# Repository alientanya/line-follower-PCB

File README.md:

# FLF Bot Modular PCB

A modular PCB platform for Fast Line Follower (FLF) robots, designed to prioritize sensor experimentation and component flexibility.
This board allows multiple sensor array designs to be used interchangeably without redesigning the core electronics.
Instead of committing to a single sensor layout, this PCB supports four distinct sensor array designs, all compatible with the same base system.

---

## Menu

- [Hardware Revisions](#hardware-revisions)
- [Repository Structure](#repository-structure)
- [Core Features](#core-features)  
- [Core Components & Design Choices](#core-components--design-choices)  
- [Sensors](#sensors)  
- [Interchangeable Sensor Arrays](#interchangeable-sensor-arrays)  
- [8+1 Sensor Placement Strategy](#81-sensor-placement-strategy)  
- [Main Control PCB](#main-control-pcb)  
- [MCU Control](#mcu-control)  
- [Detailed Module Documentation](#detailed-module-documentation)
- [Design Considerations](#design-considerations)  
- [License](#license)

---

## Hardware Revisions

- **Lavender 1.0 (Blackpill version)** —   
  Fully designed, fabricated, assembled, and successfully deployed on the physical FLF robot. Uses the STM32F411 Blackpill module.
- **Lavender 2.0 (IC version)** —   
  Work-in-progress experimental design integrating a discrete STM32F411 IC directly onto the PCB.

---

## Repository Structure

```text
├── Lavender 1.0 (Blackpill vers)/    # Hardware-verified revision used on the physical robot
│   ├── line follower simple.kicad_pcb # Main body PCB layout
│   ├── line follower simple.kicad_sch # Main body schematic
│   ├── QRE1113.kicad_sch              # 16-Sensor QRE1113 schematic
│   ├── TCRT_sensors.kicad_sch         # 9-Sensor TCRT5000 schematic
│   ├── customssensor.kicad_sch        # Custom IR LED + PT334 schematic
│   ├── layerconnect.kicad_sch         # Inter-board connector schematic
│   └── FLF_gerbers/                   # Production Gerber output files
├── Lavender 2.0 (IC vers)/           # WIP prototype with discrete STM32 IC
│   ├── STMf411.kicad_sch              # Discrete STM32F411 MCU schematic
│   └── line follower simple.kicad_pcb # 2.0 PCB layout (WIP)
├── PCB customs/                       # 3D STEP models & custom KiCad footprint libraries
├── docs/                              # Detailed hardware documentation guides
│   ├── MODULES.md                     # Circuit modules & subsystem technical reference
│   ├── SENSOR_ARRAYS.md               # Sensor array designs & 8+1 strategy guide
│   └── PINOUTS_AND_REVISIONS.md       # Pin mapping & revision comparison guide
├── images/                            # PCB renders and schematic diagrams
├── LICENSE                            # MIT License
└── README.md                          # Main project README
```

---

## Core Features

* 4 interchangeable sensor array designs
* Modular architecture using headers
* STM32F411 (Blackpill) based control (Lavender 1.0)
* HC-05 Bluetooth connectivity
* Stackable PCB with internal battery space

---

## Core Components & Design Choices

### Microcontroller —  (Blackpill)

* High-speed ADC for sensor reading
* Rich GPIO availability
* Hardware timers for motor PWM
* Plug-in module → easy replacement

---

### Motor Driver — 

* Dual DC motor driver
* Efficient and compact
* Suitable for N20 motors

---

### Voltage Regulation — 

* Buck converter → stable 3.3V
* High efficiency for battery operation
* Adjustable output

---

### Communication — 

* UART-based Bluetooth module
* Used for debugging and tuning
* Supports STATE and EN pins

---

### Analog Multiplexer — 

* 16-channel analog MUX
* Used in high-density sensor configuration
* Reduces MCU pin usage

---

## Sensors

#### 

* Compact reflective IR sensor
* Fast response
* Used in high-density and simple arrays

#### 

* Larger footprint
* More tolerant of alignment and height

#### 

* Discrete design
* Custom Sensors
* Fully tunable sensitivity

---

## Interchangeable Sensor Arrays

All arrays share a common connector interface, making them plug-and-play.

### 1. 16-Sensor Curved Array (QRE1113 + MUX)

* High resolution                            
* Uses 74HC4067
* Designed for aggressive curves

### 2. 9-Sensor Straight Array (QRE1113)

* Direct MCU input
* Low latency
* Simpler processing

### 3. 9-Sensor Curved Array (TCRT5000)

* Better surface tolerance
* Slight curvature improves tracking

### 4. Custom Sensor Array

* IR LED + PT334-6C
* Fully customizable behaviour

---

## 8+1 Sensor Placement Strategy

* 8 main sensors → line tracking
* +1 front sensor → overshoot detection

Improves turning accuracy at high speed.

---

## MCU Control

The STM32F411 (Blackpill) acts as the central controller, interfacing with sensors, motor driver, and Bluetooth module.

* Reads sensor data:

  * Direct ADC (for 9-sensor arrays)
  * Via 74HC4067 MUX (for 16-sensor array)
* Processes line position
* Controls motors using PWM + direction pins (TB6612FNG)
* Handles UART communication with HC-05

All sensor arrays use a consistent interface, so firmware changes are minimal when switching configurations.

---

## Main Control PCB

This section describes the core board that handles control, power distribution, and user interaction.

* Hosts the STM32F411 (Blackpill), TB6612FNG motor driver, and HC-05 module
* Separates logic and motor power to reduce noise interference
* Includes dual switches:
  * Motor Kill
  * Battery Kill

* Provides connectors for all interchangeable sensor arrays
* Routes sensor signals (direct or via MUX) to the MCU
* Includes 2 push buttons:
  * Used for control, mode selection, and calibration
  * Hardware debounced (RC)
* Designed as part of a stacked PCB system:
  * Interfaces with the top board via pin headers
  * Creates space between layers for battery placement

---

## Detailed Module Documentation

Explore the dedicated hardware documentation guides for in-depth schematic breakdowns, pinout mappings, and circuit specifications:

- 🔌 **[Circuit Modules & Subsystems Guide](docs/MODULES.md)** — Technical reference for Power Management & Rail Isolation, MCU & SWD Debugging, TB6612FNG Motor Driver, 74HC4067 MUX, Emitter Biasing, RC Hardware Debouncing, and the Inter-Board Header Bus.
- 🎯 **[Interchangeable Sensor Arrays & Placement Strategy](docs/SENSOR_ARRAYS.md)** — Comprehensive breakdown of the 4 sensor array variants (16-QRE MUX, 9-QRE, 9-TCRT, Custom Discrete) and the 8+1 apex placement geometry.
- 📌 **[Pin Mapping & Hardware Revisions Guide](docs/PINOUTS_AND_REVISIONS.md)** — Hardware peripheral pin assignments (PWM, ADC, MUX select, UART), SWD interface, and comparison between Lavender 1.0 (Field-Tested) and Lavender 2.0 (WIP).

---

## Design Considerations

- Tradeoff between sensor resolution and sampling speed (MUX vs direct ADC)
- Separation of motor and logic power to reduce noise
- Modular sensor interface to allow rapid hardware iteration
- Use of off-the-shelf modules (MCU, driver, regulator) for reliability and easy replacement
- Support for multiple sensor geometries to evaluate performance under different track conditions

---

## Summary

Instead of locking the design into a single sensor configuration, this PCB is built as a flexible platform that encourages rapid experimentation and iteration. Supporting multiple interchangeable sensor arrays, it allows direct comparison between different sensing approaches, geometries, and component choices under the same hardware conditions. This makes it easier to fine-tune performance, optimise control algorithms, and adapt the system for different track types. Ultimately, the goal of this design is not just to work, but to provide a reliable foundation for continuously improving and pushing the limits of FLF performance.

---

## License

This project is licensed under the MIT License — see the [LICENSE](LICENSE) file for details.

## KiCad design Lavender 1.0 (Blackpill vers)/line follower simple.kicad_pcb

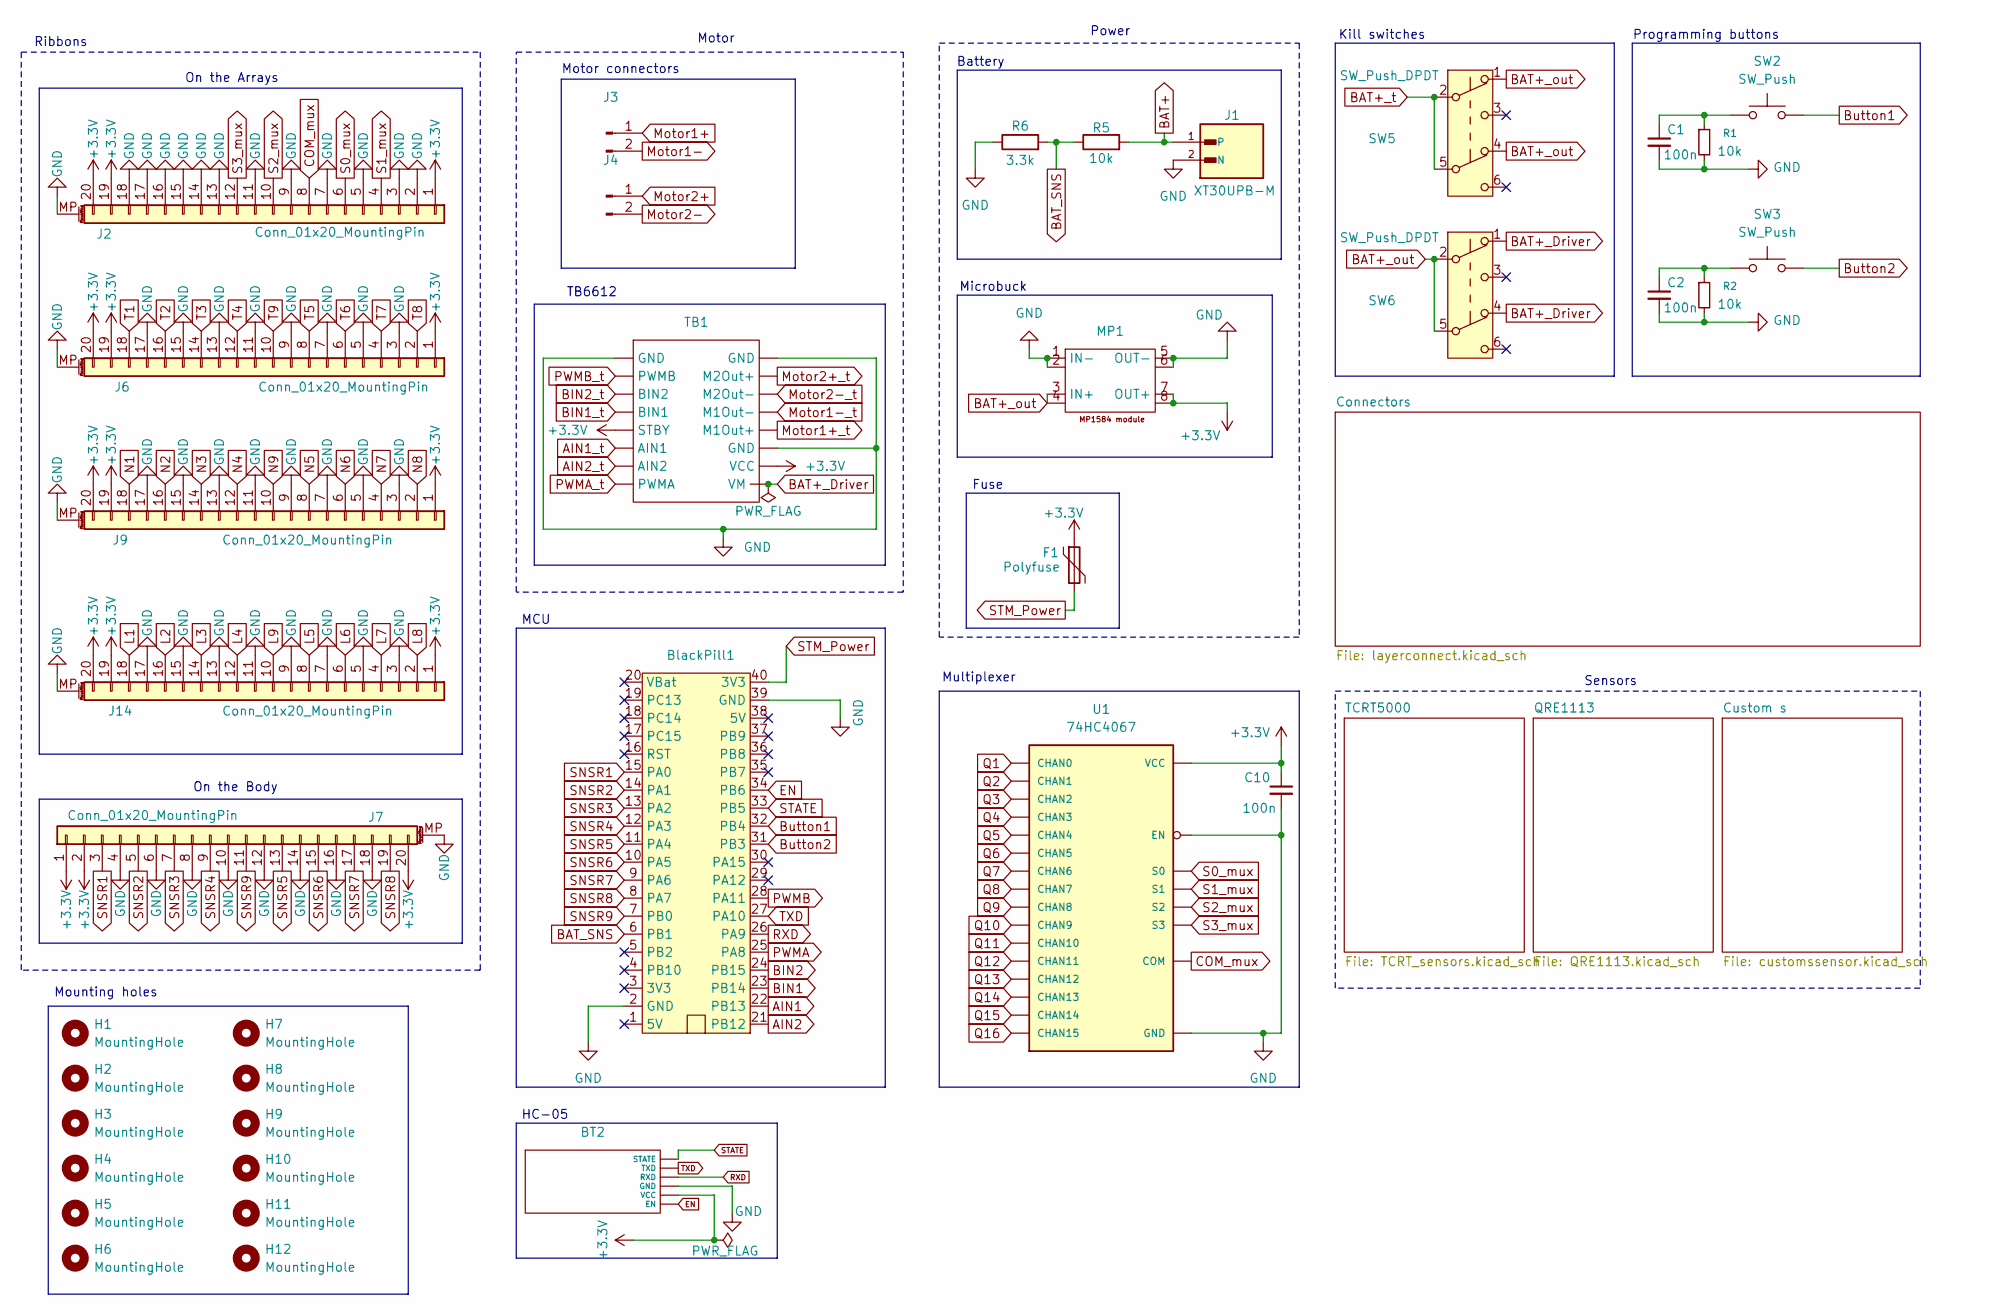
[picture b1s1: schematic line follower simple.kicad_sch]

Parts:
BT2: PinSocket_1x06_P2.54mm_Vertical
BlackPill1: STM32F411_BP; blackpill_fp
C1, C2, C10: 100n; C_0603_1608Metric_Pad1.08x0.95mm_HandSolder
F1: Polyfuse; Fuse_0805_2012Metric_Pad1.15x1.40mm_HandSolder
H1, H2, H3, H4, H5, H6, H7, H8, H9, H10, H11, H12: MountingHole; 2mm hole
J1: XT30UPB-M; AMASS_XT30UPB-M_1x02_P5.0mm_Vertical
J2, J6, J7, J9, J14: Conn_01x20_MountingPin; Amphenol_F32Q-1A7x1-11020_1x20-1MP_P0.5mm_Horizontal
J3, J4: Conn_01x02_Pin; JST_PH_B2B-PH-K_1x02_P2.00mm_Vertical
MP1: MP1584_fp
R1, R2, R5: 10k; R_0603_1608Metric_Pad0.98x0.95mm_HandSolder
R6: 3.3k; R_0603_1608Metric_Pad0.98x0.95mm_HandSolder
SW2, SW3: SW_Push; Push button-fp
SW5, SW6: SW_Push_DPDT; SW_Push_2P2T_Toggle_CK_PVA2xxH3xxxxxxV2
TB1: TB6612 module
U1: 74HC4067; 74HC4067-Mux

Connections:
+3.3V: BT2.5 (VCC), C10.1, F1.1, J2.1, J2.19, J2.20, J6.1, J6.19, J6.20, J7.1, J7.2, J7.20, J9.1, J9.19, J9.20, J14.1, J14.19, J14.20, MP1.7 (OUT+), MP1.8, TB1.5 (STBY), TB1.15 (VCC), U1.P24 (VCC); also elsewhere on the board
AIN1: BlackPill1.22 (PB13); also elsewhere on the board
AIN1_t: TB1.6 (AIN1); also elsewhere on the board
AIN2: BlackPill1.21 (PB12); also elsewhere on the board
AIN2_t: TB1.7 (AIN2); also elsewhere on the board
BAT+: J1.1, R5.2; also elsewhere on the board
BAT+_Driver: SW6.1 (A), SW6.4 (A), TB1.16 (VM)
BAT+_out: MP1.3 (IN+), MP1.4, SW5.1 (A), SW5.4 (A), SW6.2 (B), SW6.5 (B)
BAT+_t: SW5.2 (B), SW5.5 (B); also elsewhere on the board
BAT_SNS: BlackPill1.6 (PB1), R5.1, R6.2
BIN1: BlackPill1.23 (PB14); also elsewhere on the board
BIN1_t: TB1.4 (BIN1); also elsewhere on the board
BIN2: BlackPill1.24 (PB15); also elsewhere on the board
BIN2_t: TB1.3 (BIN2); also elsewhere on the board
Button1: BlackPill1.32 (PB4), SW2.2
Button2: BlackPill1.31 (PB3), SW3.2
COM_mux: J2.8, U1.P1 (COM); also elsewhere on the board
EN: BT2.6 (EN), BlackPill1.34 (PB6)
GND: BT2.4 (GND), BlackPill1.2 (GND), BlackPill1.39 (GND), C1.2, C2.2, C10.2, J1.2 (N), J2.2, J2.3, J2.5, J2.7, J2.9, J2.11, J2.13, J2.14, J2.15, J2.16, J2.17, J2.18, J2.MP (MountPin), J6.3, J6.5, J6.7, J6.9, J6.11, J6.13, J6.15, J6.17, J6.MP (MountPin), J7.4, J7.6, J7.8, J7.10, J7.12, J7.14, J7.16, J7.18, J7.MP (MountPin), J9.3, J9.5, J9.7, J9.9, J9.11, J9.13, J9.15, J9.17, J9.MP (MountPin), J14.3, J14.5, J14.7, J14.9, J14.11, J14.13, J14.15, J14.17, J14.MP (MountPin), MP1.1 (IN-), MP1.2, MP1.5 (OUT-), MP1.6, R1.2, R2.2, R6.1, TB1.1 (GND), TB1.9 (GND), TB1.14 (GND), U1.P12 (GND), U1.P15 (EN); also elsewhere on the board
Motor1+: J3.1; also elsewhere on the board
Motor1+_t: TB1.13 (M1Out+); also elsewhere on the board
Motor1-: J3.2; also elsewhere on the board
Motor1-_t: TB1.12 (M1Out-); also elsewhere on the board
Motor2+: J4.1; also elsewhere on the board
Motor2+_t: TB1.10 (M2Out+); also elsewhere on the board
Motor2-: J4.2; also elsewhere on the board
Motor2-_t: TB1.11 (M2Out-); also elsewhere on the board
N1: J9.18; also elsewhere on the board
N2: J9.16; also elsewhere on the board
N3: J9.14; also elsewhere on the board
N4: J9.12; also elsewhere on the board
N5: J9.8; also elsewhere on the board
N6: J9.6; also elsewhere on the board
N7: J9.4; also elsewhere on the board
N8: J9.2; also elsewhere on the board
N9: J9.10; also elsewhere on the board
unnamed: C1.1, R1.1, SW2.1
unnamed: C2.1, R2.1, SW3.1
PWMA: BlackPill1.25 (PA8); also elsewhere on the board
PWMA_t: TB1.8 (PWMA); also elsewhere on the board
PWMB: BlackPill1.28 (PA11); also elsewhere on the board
PWMB_t: TB1.2 (PWMB); also elsewhere on the board
Q1: U1.P9 (CHAN0); also elsewhere on the board
Q2: U1.P8 (CHAN1); also elsewhere on the board
Q3: U1.P7 (CHAN2); also elsewhere on the board
Q4: U1.P6 (CHAN3); also elsewhere on the board
Q5: U1.P5 (CHAN4); also elsewhere on the board
Q6: U1.P4 (CHAN5); also elsewhere on the board
Q7: U1.P3 (CHAN6); also elsewhere on the board
Q8: U1.P2 (CHAN7); also elsewhere on the board
Q9: U1.P23 (CHAN8); also elsewhere on the board
Q10: U1.P22 (CHAN9); also elsewhere on the board
Q11: U1.P21 (CHAN10); also elsewhere on the board
Q12: U1.P20 (CHAN11); also elsewhere on the board
Q13: U1.P19 (CHAN12); also elsewhere on the board
Q14: U1.P18 (CHAN13); also elsewhere on the board
Q15: U1.P17 (CHAN14); also elsewhere on the board
Q16: U1.P16 (CHAN15); also elsewhere on the board
RXD: BT2.3 (RXD), BlackPill1.26 (PA9)
S0_mux: J2.6, U1.P10 (S0); also elsewhere on the board
S1_mux: J2.4, U1.P11 (S1); also elsewhere on the board
S2_mux: J2.10, U1.P14 (S2); also elsewhere on the board
S3_mux: J2.12, U1.P13 (S3); also elsewhere on the board
SNSR1: BlackPill1.15 (PA0), J7.3; also elsewhere on the board
SNSR2: BlackPill1.14 (PA1), J7.5; also elsewhere on the board
SNSR3: BlackPill1.13 (PA2), J7.7; also elsewhere on the board
SNSR4: BlackPill1.12 (PA3), J7.9; also elsewhere on the board
SNSR5: BlackPill1.11 (PA4), J7.13; also elsewhere on the board
SNSR6: BlackPill1.10 (PA5), J7.15; also elsewhere on the board
SNSR7: BlackPill1.9 (PA6), J7.17; also elsewhere on the board
SNSR8: BlackPill1.8 (PA7), J7.19; also elsewhere on the board
SNSR9: BlackPill1.7 (PB0), J7.11; also elsewhere on the board
STATE: BT2.1 (STATE), BlackPill1.33 (PB5)
STM_Power: BlackPill1.40 (3V3), F1.2
T1: J6.18; also elsewhere on the board
T2: J6.16; also elsewhere on the board
T3: J6.14; also elsewhere on the board
T4: J6.12; also elsewhere on the board
T5: J6.8; also elsewhere on the board
T6: J6.6; also elsewhere on the board
T7: J6.4; also elsewhere on the board
T8: J6.2; also elsewhere on the board
T9: J6.10; also elsewhere on the board
TXD: BT2.2 (TXD), BlackPill1.27 (PA10)

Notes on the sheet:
Kill switches
On the Body
Sensors
Mounting holes
Programming buttons
Fuse
Battery
Power
On the Arrays
Microbuck
Ribbons
Motor
TB6612
MCU
Motor connectors
Multiplexer
HC-05

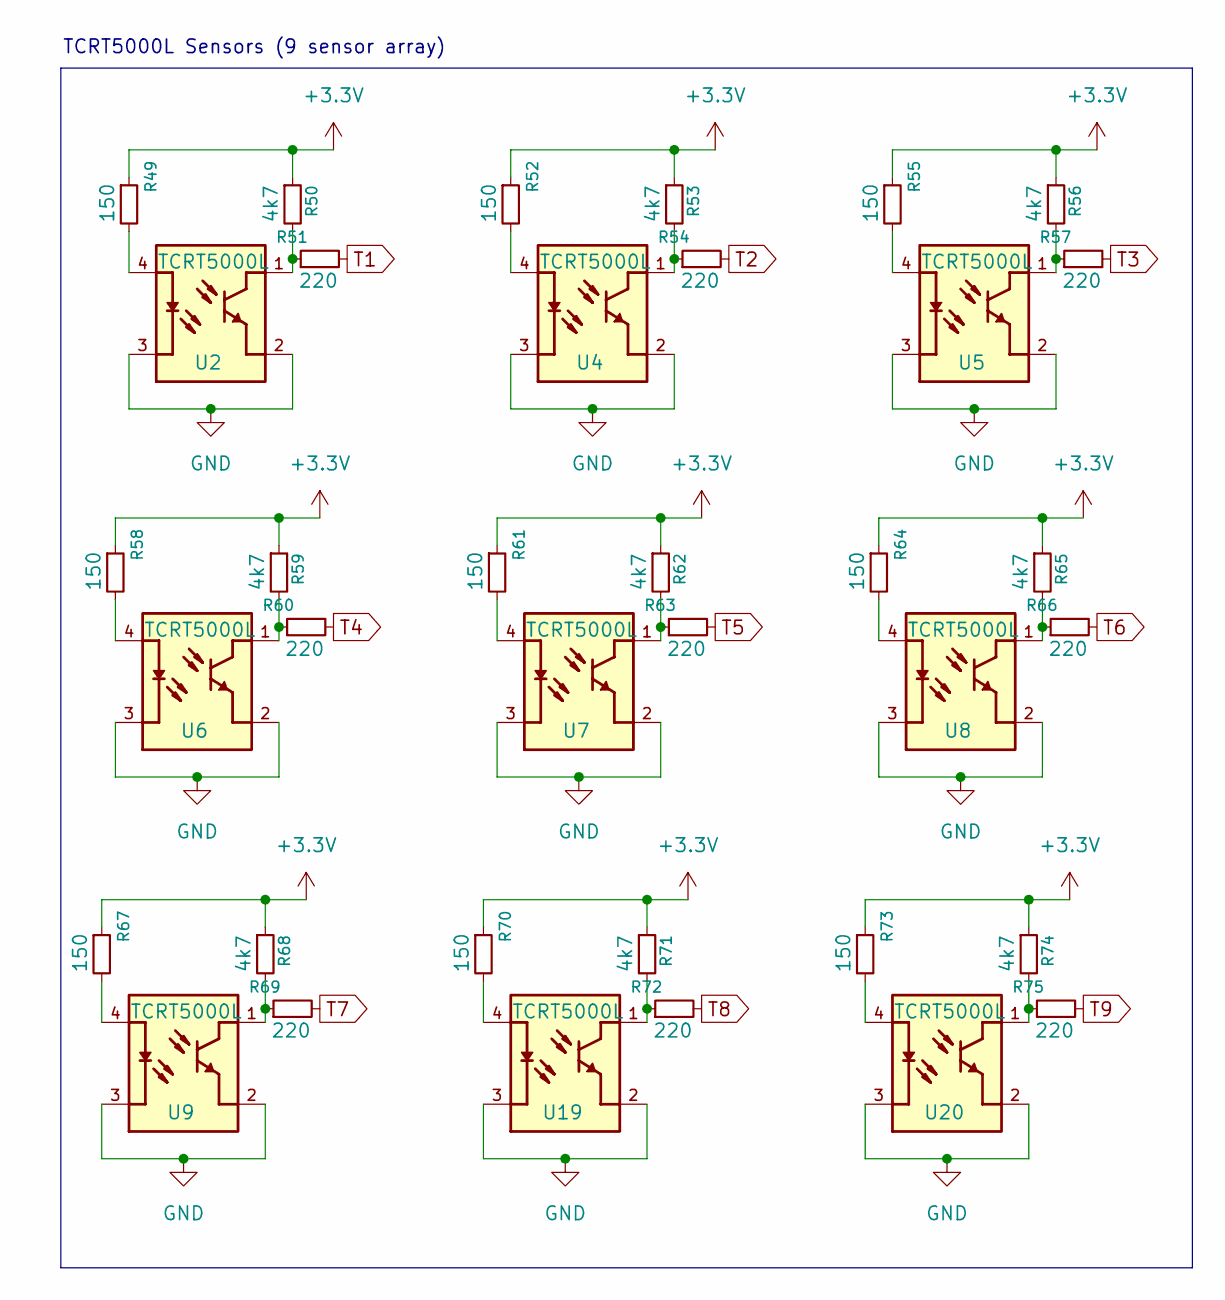
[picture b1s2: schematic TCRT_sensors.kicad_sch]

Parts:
R49, R52, R55, R58, R61, R64, R67, R70, R73: 150; R_0603_1608Metric_Pad0.98x0.95mm_HandSolder
R50, R53, R56, R59, R62, R65, R68, R71, R74: 4k7; R_0603_1608Metric_Pad0.98x0.95mm_HandSolder
R51, R54, R57, R60, R63, R66, R69, R72, R75: 220; R_0603_1608Metric_Pad0.98x0.95mm_HandSolder
U2, U4, U5, U6, U7, U8, U9, U19, U20: TCRT5000L; XDCR_TCRT5000L

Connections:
+3.3V: R49.1, R50.1, R52.1, R53.1, R55.1, R56.1, R58.1, R59.1, R61.1, R62.1, R64.1, R65.1, R67.1, R68.1, R70.1, R71.1, R73.1, R74.1; also elsewhere on the board
GND: U2.2, U2.3, U4.2, U4.3, U5.2, U5.3, U6.2, U6.3, U7.2, U7.3, U8.2, U8.3, U9.2, U9.3, U19.2, U19.3, U20.2, U20.3; also elsewhere on the board
unnamed: R49.2, U2.4
unnamed: R50.2, R51.1, U2.1
unnamed: R52.2, U4.4
unnamed: R53.2, R54.1, U4.1
unnamed: R55.2, U5.4
unnamed: R56.2, R57.1, U5.1
unnamed: R58.2, U6.4
unnamed: R59.2, R60.1, U6.1
unnamed: R61.2, U7.4
unnamed: R62.2, R63.1, U7.1
unnamed: R64.2, U8.4
unnamed: R65.2, R66.1, U8.1
unnamed: R67.2, U9.4
unnamed: R68.2, R69.1, U9.1
unnamed: R70.2, U19.4
unnamed: R71.2, R72.1, U19.1
unnamed: R73.2, U20.4
unnamed: R74.2, R75.1, U20.1
T1: R51.2; also elsewhere on the board
T2: R54.2; also elsewhere on the board
T3: R57.2; also elsewhere on the board
T4: R60.2; also elsewhere on the board
T5: R63.2; also elsewhere on the board
T6: R66.2; also elsewhere on the board
T7: R69.2; also elsewhere on the board
T8: R72.2; also elsewhere on the board
T9: R75.2; also elsewhere on the board

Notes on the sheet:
TCRT5000L Sensors (9 sensor array)

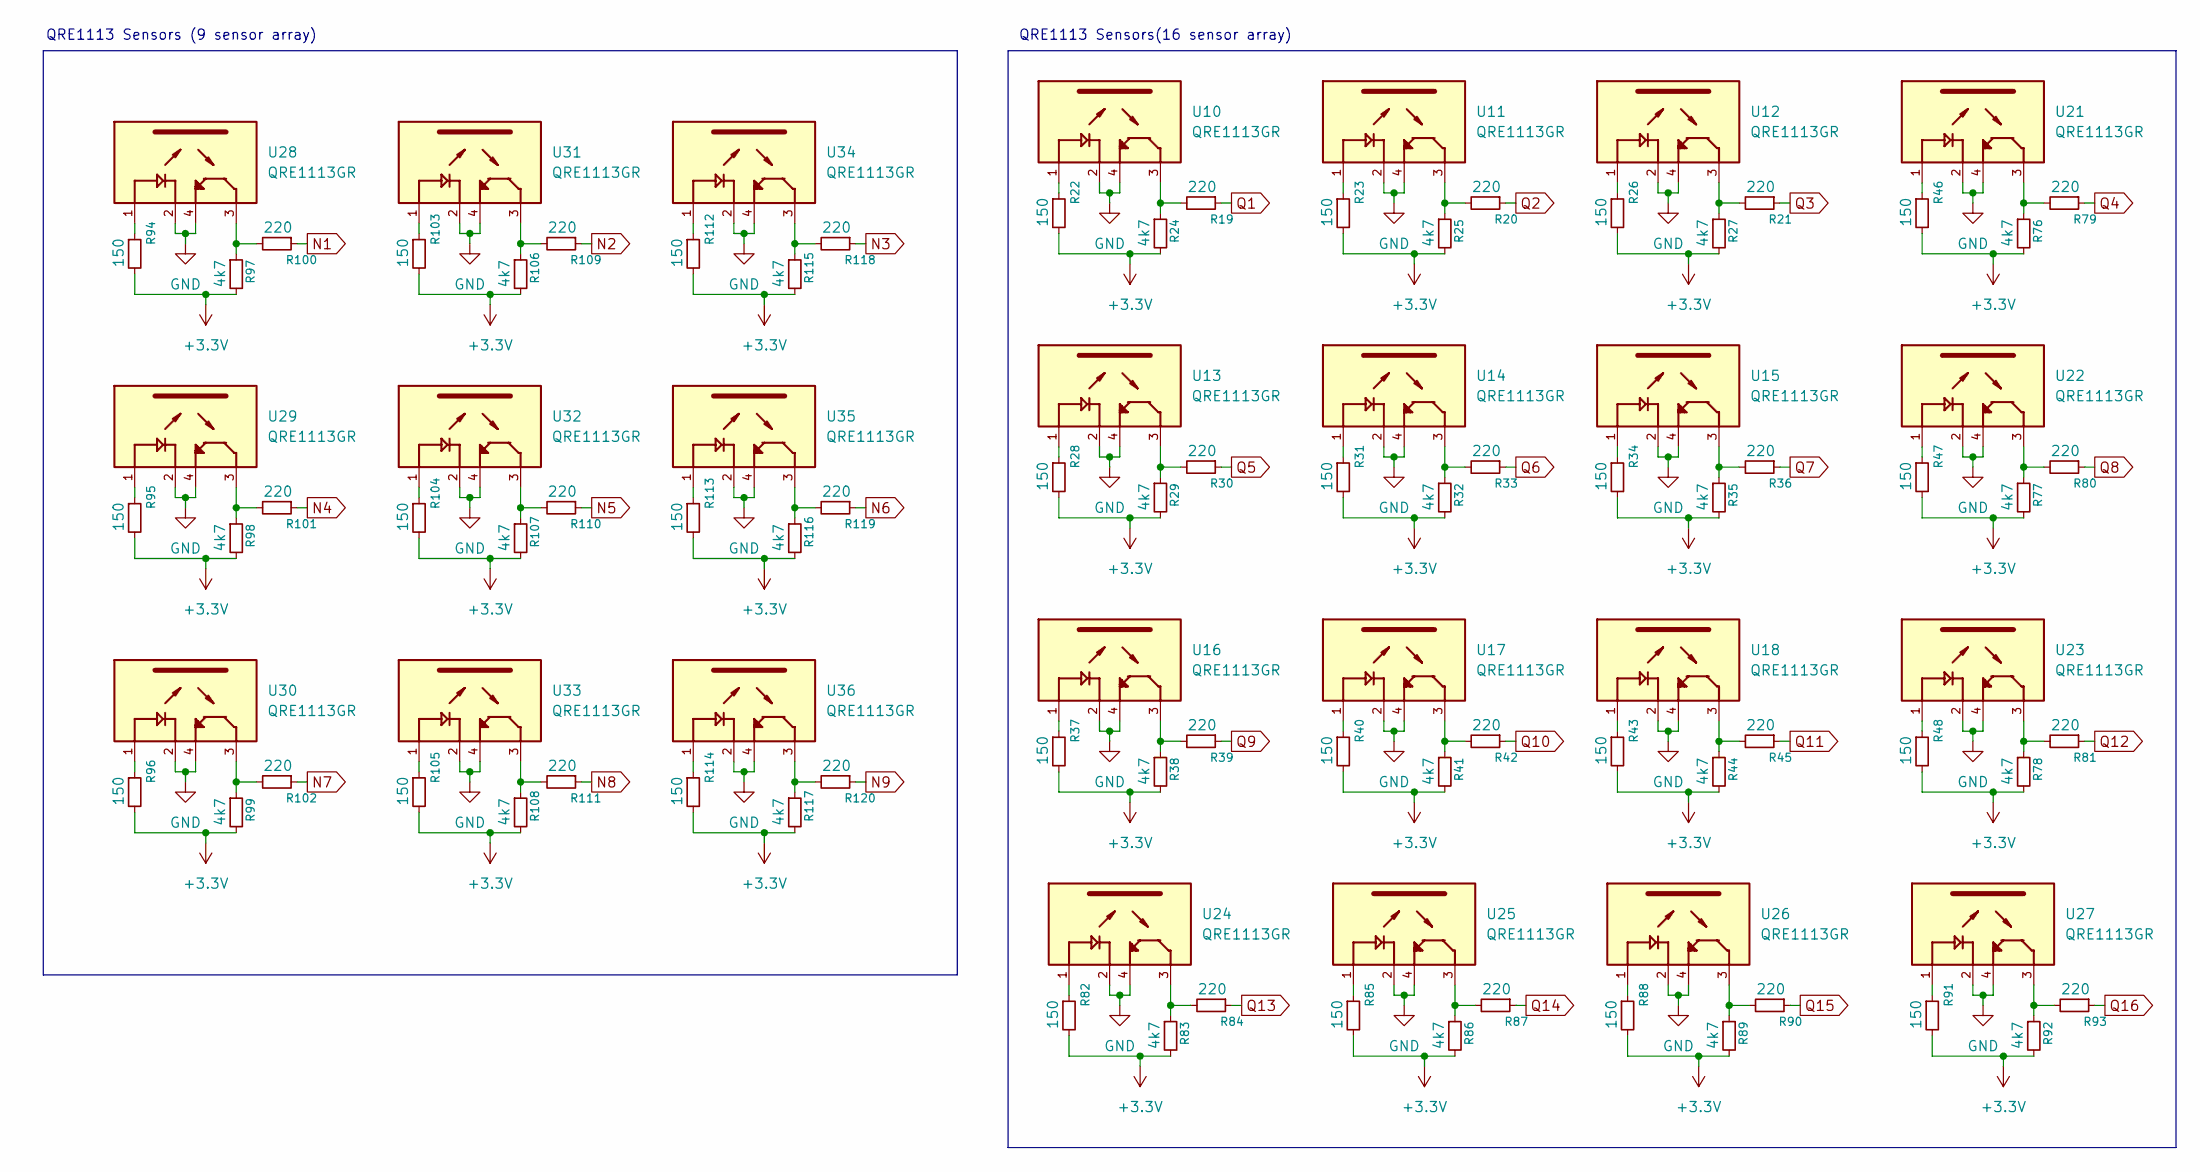
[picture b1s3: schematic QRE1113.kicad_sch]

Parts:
R19, R20, R21, R30, R33, R36, R39, R42, R45, R79, R80, R81, R84, R87, R90, R93, R100, R101, R102, R109, R110, R111, R118, R119, R120: 220; R_0603_1608Metric_Pad0.98x0.95mm_HandSolder
R22, R23, R26, R28, R31, R34, R37, R40, R43, R46, R47, R48, R82, R85, R88, R91, R94, R95, R96, R103, R104, R105, R112, R113, R114: 150; R_0603_1608Metric_Pad0.98x0.95mm_HandSolder
R24, R25, R27, R29, R32, R35, R38, R41, R44, R76, R77, R78, R83, R86, R89, R92, R97, R98, R99, R106, R107, R108, R115, R116, R117: 4k7; R_0603_1608Metric_Pad0.98x0.95mm_HandSolder
U10, U11, U12, U13, U14, U15, U16, U17, U18, U21, U22, U23, U24, U25, U26, U27, U28, U29, U30, U31, U32, U33, U34, U35, U36: QRE1113GR; QRE1113-SMD; PARTREV 5

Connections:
+3.3V: R22.2, R23.2, R24.2, R25.2, R26.2, R27.2, R28.2, R29.2, R31.2, R32.2, R34.2, R35.2, R37.2, R38.2, R40.2, R41.2, R43.2, R44.2, R46.2, R47.2, R48.2, R76.2, R77.2, R78.2, R82.2, R83.2, R85.2, R86.2, R88.2, R89.2, R91.2, R92.2, R94.2, R95.2, R96.2, R97.2, R98.2, R99.2, R103.2, R104.2, R105.2, R106.2, R107.2, R108.2, R112.2, R113.2, R114.2, R115.2, R116.2, R117.2; also elsewhere on the board
GND: U10.2, U10.4, U11.2, U11.4, U12.2, U12.4, U13.2, U13.4, U14.2, U14.4, U15.2, U15.4, U16.2, U16.4, U17.2, U17.4, U18.2, U18.4, U21.2, U21.4, U22.2, U22.4, U23.2, U23.4, U24.2, U24.4, U25.2, U25.4, U26.2, U26.4, U27.2, U27.4, U28.2, U28.4, U29.2, U29.4, U30.2, U30.4, U31.2, U31.4, U32.2, U32.4, U33.2, U33.4, U34.2, U34.4, U35.2, U35.4, U36.2, U36.4; also elsewhere on the board
N1: R100.1; also elsewhere on the board
N2: R109.1; also elsewhere on the board
N3: R118.1; also elsewhere on the board
N4: R101.1; also elsewhere on the board
N5: R110.1; also elsewhere on the board
N6: R119.1; also elsewhere on the board
N7: R102.1; also elsewhere on the board
N8: R111.1; also elsewhere on the board
N9: R120.1; also elsewhere on the board
unnamed: R19.2, R24.1, U10.3
unnamed: R20.2, R25.1, U11.3
unnamed: R21.2, R27.1, U12.3
unnamed: R22.1, U10.1
unnamed: R23.1, U11.1
unnamed: R26.1, U12.1
unnamed: R28.1, U13.1
unnamed: R29.1, R30.2, U13.3
unnamed: R31.1, U14.1
unnamed: R32.1, R33.2, U14.3
unnamed: R34.1, U15.1
unnamed: R35.1, R36.2, U15.3
unnamed: R37.1, U16.1
unnamed: R38.1, R39.2, U16.3
unnamed: R40.1, U17.1
unnamed: R41.1, R42.2, U17.3
unnamed: R43.1, U18.1
unnamed: R44.1, R45.2, U18.3
unnamed: R46.1, U21.1
unnamed: R47.1, U22.1
unnamed: R48.1, U23.1
unnamed: R76.1, R79.2, U21.3
unnamed: R77.1, R80.2, U22.3
unnamed: R78.1, R81.2, U23.3
unnamed: R82.1, U24.1
unnamed: R83.1, R84.2, U24.3
unnamed: R85.1, U25.1
unnamed: R86.1, R87.2, U25.3
unnamed: R88.1, U26.1
unnamed: R89.1, R90.2, U26.3
unnamed: R91.1, U27.1
unnamed: R92.1, R93.2, U27.3
unnamed: R94.1, U28.1
unnamed: R95.1, U29.1
unnamed: R96.1, U30.1
unnamed: R97.1, R100.2, U28.3
unnamed: R98.1, R101.2, U29.3
unnamed: R99.1, R102.2, U30.3
unnamed: R103.1, U31.1
unnamed: R104.1, U32.1
unnamed: R105.1, U33.1
unnamed: R106.1, R109.2, U31.3
unnamed: R107.1, R110.2, U32.3
unnamed: R108.1, R111.2, U33.3
unnamed: R112.1, U34.1
unnamed: R113.1, U35.1
unnamed: R114.1, U36.1
unnamed: R115.1, R118.2, U34.3
unnamed: R116.1, R119.2, U35.3
unnamed: R117.1, R120.2, U36.3
Q1: R19.1; also elsewhere on the board
Q2: R20.1; also elsewhere on the board
Q3: R21.1; also elsewhere on the board
Q4: R79.1; also elsewhere on the board
Q5: R30.1; also elsewhere on the board
Q6: R33.1; also elsewhere on the board
Q7: R36.1; also elsewhere on the board
Q8: R80.1; also elsewhere on the board
Q9: R39.1; also elsewhere on the board
Q10: R42.1; also elsewhere on the board
Q11: R45.1; also elsewhere on the board
Q12: R81.1; also elsewhere on the board
Q13: R84.1; also elsewhere on the board
Q14: R87.1; also elsewhere on the board
Q15: R90.1; also elsewhere on the board
Q16: R93.1; also elsewhere on the board

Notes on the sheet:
QRE1113 Sensors (9 sensor array)
QRE1113 Sensors(16 sensor array)

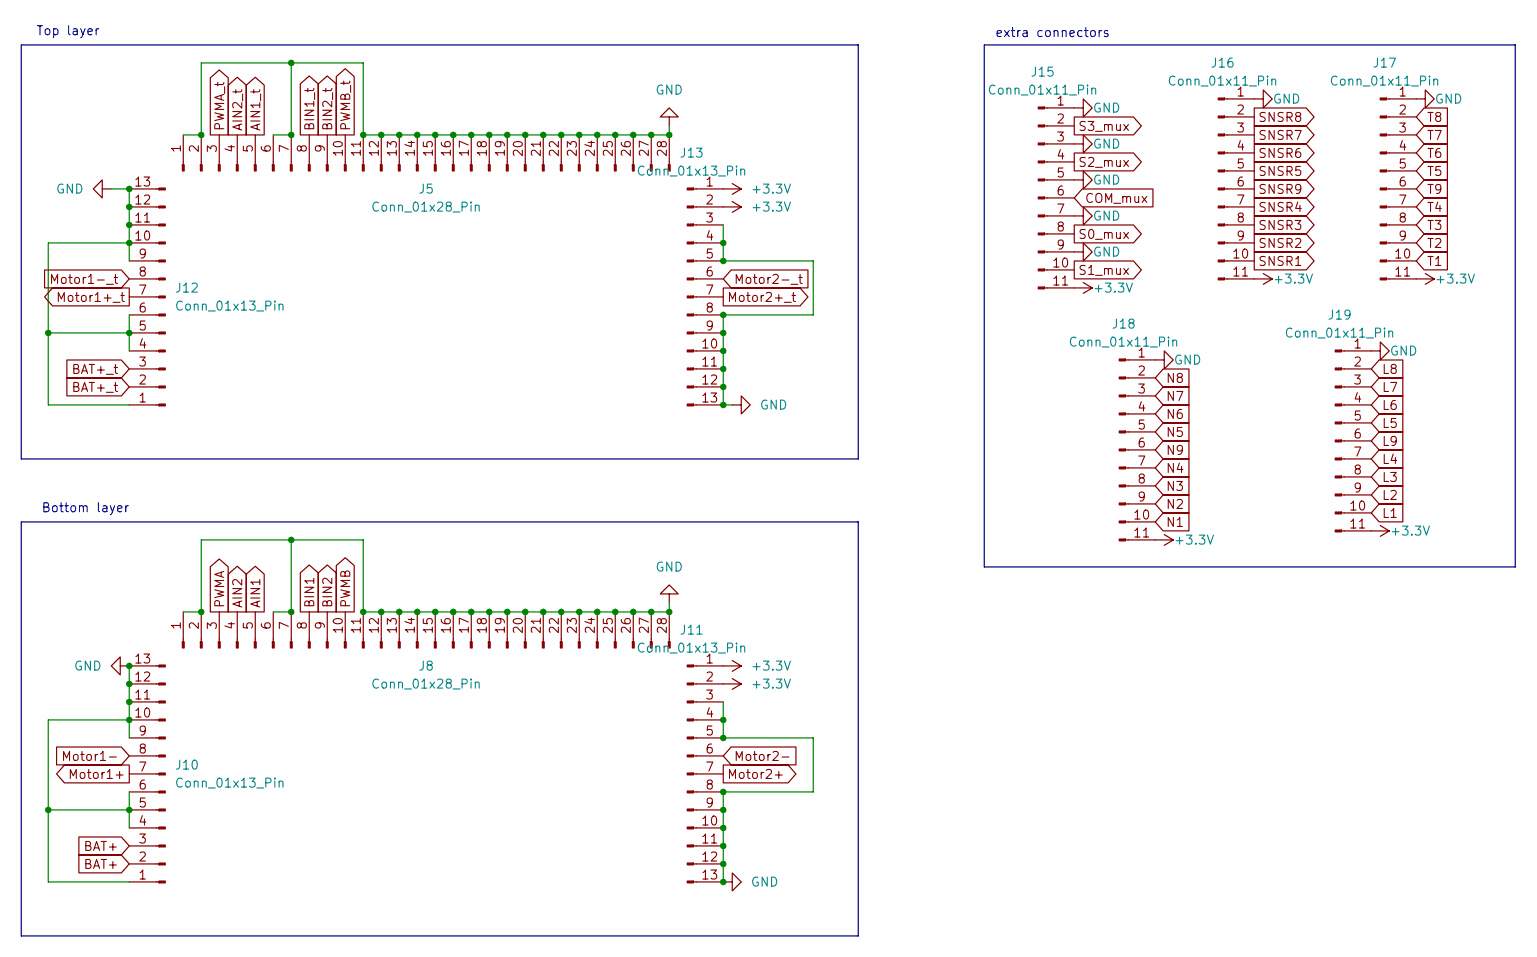
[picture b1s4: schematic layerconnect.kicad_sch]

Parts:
J5, J8: Conn_01x28_Pin; PinHeader_1x28_P2.54mm_Vertical
J10, J11, J12, J13: Conn_01x13_Pin; PinHeader_1x13_P2.54mm_Vertical
J15, J16, J17, J18, J19: Conn_01x11_Pin; PinHeader_1x11_P2.54mm_Vertical

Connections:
+3.3V: J11.1, J11.2, J13.1, J13.2, J15.11, J16.11, J17.11, J18.11, J19.11; also elsewhere on the board
AIN1: J8.5; also elsewhere on the board
AIN1_t: J5.5; also elsewhere on the board
AIN2: J8.4; also elsewhere on the board
AIN2_t: J5.4; also elsewhere on the board
BAT+: J10.2, J10.3; also elsewhere on the board
BAT+_t: J12.2, J12.3; also elsewhere on the board
BIN1: J8.8; also elsewhere on the board
BIN1_t: J5.8; also elsewhere on the board
BIN2: J8.9; also elsewhere on the board
BIN2_t: J5.9; also elsewhere on the board
COM_mux: J15.6; also elsewhere on the board
GND: J5.1, J5.2, J5.6, J5.7, J5.11, J5.12, J5.13, J5.14, J5.15, J5.16, J5.17, J5.18, J5.19, J5.20, J5.21, J5.22, J5.23, J5.24, J5.25, J5.26, J5.27, J5.28, J8.1, J8.2, J8.6, J8.7, J8.11, J8.12, J8.13, J8.14, J8.15, J8.16, J8.17, J8.18, J8.19, J8.20, J8.21, J8.22, J8.23, J8.24, J8.25, J8.26, J8.27, J8.28, J10.1, J10.4, J10.5, J10.6, J10.9, J10.10, J10.11, J10.12, J10.13, J11.3, J11.4, J11.5, J11.8, J11.9, J11.10, J11.11, J11.12, J11.13, J12.1, J12.4, J12.5, J12.6, J12.9, J12.10, J12.11, J12.12, J12.13, J13.3, J13.4, J13.5, J13.8, J13.9, J13.10, J13.11, J13.12, J13.13, J15.1, J15.3, J15.5, J15.7, J15.9, J16.1, J17.1, J18.1, J19.1; also elsewhere on the board
Motor1+: J10.7; also elsewhere on the board
Motor1+_t: J12.7; also elsewhere on the board
Motor1-: J10.8; also elsewhere on the board
Motor1-_t: J12.8; also elsewhere on the board
Motor2+: J11.7; also elsewhere on the board
Motor2+_t: J13.7; also elsewhere on the board
Motor2-: J11.6; also elsewhere on the board
Motor2-_t: J13.6; also elsewhere on the board
N1: J18.10; also elsewhere on the board
N2: J18.9; also elsewhere on the board
N3: J18.8; also elsewhere on the board
N4: J18.7; also elsewhere on the board
N5: J18.5; also elsewhere on the board
N6: J18.4; also elsewhere on the board
N7: J18.3; also elsewhere on the board
N8: J18.2; also elsewhere on the board
N9: J18.6; also elsewhere on the board
PWMA: J8.3; also elsewhere on the board
PWMA_t: J5.3; also elsewhere on the board
PWMB: J8.10; also elsewhere on the board
PWMB_t: J5.10; also elsewhere on the board
S0_mux: J15.8; also elsewhere on the board
S1_mux: J15.10; also elsewhere on the board
S2_mux: J15.4; also elsewhere on the board
S3_mux: J15.2; also elsewhere on the board
SNSR1: J16.10; also elsewhere on the board
SNSR2: J16.9; also elsewhere on the board
SNSR3: J16.8; also elsewhere on the board
SNSR4: J16.7; also elsewhere on the board
SNSR5: J16.5; also elsewhere on the board
SNSR6: J16.4; also elsewhere on the board
SNSR7: J16.3; also elsewhere on the board
SNSR8: J16.2; also elsewhere on the board
SNSR9: J16.6; also elsewhere on the board
T1: J17.10; also elsewhere on the board
T2: J17.9; also elsewhere on the board
T3: J17.8; also elsewhere on the board
T4: J17.7; also elsewhere on the board
T5: J17.5; also elsewhere on the board
T6: J17.4; also elsewhere on the board
T7: J17.3; also elsewhere on the board
T8: J17.2; also elsewhere on the board
T9: J17.6; also elsewhere on the board

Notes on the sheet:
Top layer
extra connectors
Bottom layer

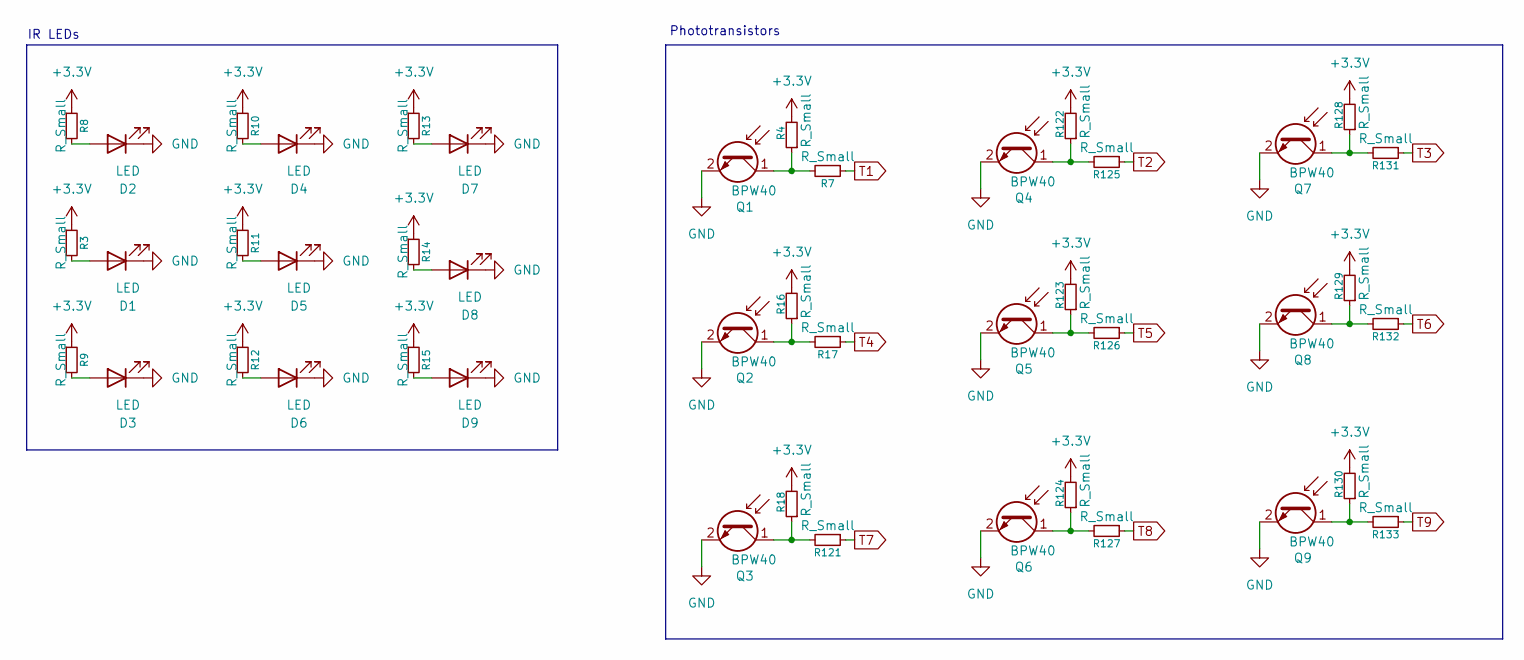
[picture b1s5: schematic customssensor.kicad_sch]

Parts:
D1, D2, D3, D4, D5, D6, D7, D8, D9: LED
Q1: BPW40; LED_D5.0mm_Horizontal_O6.35mm_Z3.0mm
Q2, Q3, Q4, Q5, Q6, Q7, Q8, Q9: BPW40; LED_D5.0mm_Clear
R3, R4, R7, R8, R9, R10, R11, R12, R13, R14, R15, R16, R17, R18, R121, R122, R123, R124, R125, R126, R127, R128, R129, R130, R131, R132, R133: R_Small; R_0603_1608Metric_Pad0.98x0.95mm_HandSolder

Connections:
+3.3V: R3.1, R4.2, R8.1, R9.1, R10.1, R11.1, R12.1, R13.1, R14.1, R15.1, R16.2, R18.2, R122.2, R123.2, R124.2, R128.2, R129.2, R130.2; also elsewhere on the board
GND: D1.1 (K), D2.1 (K), D3.1 (K), D4.1 (K), D5.1 (K), D6.1 (K), D7.1 (K), D8.1 (K), D9.1 (K), Q1.2 (E), Q2.2 (E), Q3.2 (E), Q4.2 (E), Q5.2 (E), Q6.2 (E), Q7.2 (E), Q8.2 (E), Q9.2 (E); also elsewhere on the board
unnamed: D1.2 (A), R3.2
unnamed: D2.2 (A), R8.2
unnamed: D3.2 (A), R9.2
unnamed: D4.2 (A), R10.2
unnamed: D5.2 (A), R11.2
unnamed: D6.2 (A), R12.2
unnamed: D7.2 (A), R13.2
unnamed: D8.2 (A), R14.2
unnamed: D9.2 (A), R15.2
unnamed: Q1.1 (C), R4.1, R7.2
unnamed: Q2.1 (C), R16.1, R17.2
unnamed: Q3.1 (C), R18.1, R121.2
unnamed: Q4.1 (C), R122.1, R125.2
unnamed: Q5.1 (C), R123.1, R126.2
unnamed: Q6.1 (C), R124.1, R127.2
unnamed: Q7.1 (C), R128.1, R131.2
unnamed: Q8.1 (C), R129.1, R132.2
unnamed: Q9.1 (C), R130.1, R133.2

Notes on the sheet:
Phototransistors
IR LEDs

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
